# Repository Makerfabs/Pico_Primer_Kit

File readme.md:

# Pico(W) Primer Kit

```c++
/*
Version:		V1.8
Author:			Vincent
Create Date:	2021/4/16
Note:
	2022/12/30	V1.8 Edit Wiki Link
	2022/10/11 	V1.7 Add project11,12
	2022/10/8 	V1.6 Update project10
	2022/9/27 	V1.5 Add PicoW support, add new Mabee CO2
	2022/9/20 	V1.4 Fix dht11 bug.
	2021/7/27 	V1.3 Add WS2812
	2021/5/24 	V1.2 Change IR to Ultar distance sensor.
	2021/5/19 	V1.1 Add 7 display example with MaBee module.
	
*/
```

[toc]

# Makerfabs

[Makerfabs home page](https://www.makerfabs.com/)

[Makerfabs Wiki](https://wiki.makerfabs.com/)

# Pico(PicoW) Primer Kit
## Intruduce

### Product Link ：

[Pico Primer Kit for Raspberry PI](https://www.makerfabs.com/raspberry-pi-pico-primer-kit.html)

[Pico W Primer Kit for Raspberry PI](https://www.makerfabs.com/pico-w-primer-kit-for-raspberry-pi.html)

### Wiki Link : 

[Pico W_Primer_kit](https://wiki.makerfabs.com/Pico_W_Primer_Kit.html)

Pico Primer Kit is the development shield of Pi Pico. It has ST7735 color screen, 3 LED lights and 3 buttons. There are multiple SPI, I2C, UART, GPIO interfaces.
Kit contains a number of MBEE series modules. Such as potentiometer, DHT11, MPU6050, relay and other modules.

**Now that we have a new kit for Pico W, we have replaced the 8266 module with Mabee CO2.**

Most routines are compatible, the only differences are those related to WiFi.

## Feature

- RP2040 microcontroller chip designed by Raspberry Pi in the United Kingdom
- Dual-core Arm Cortex M0+ processor, the flexible clock running up to 133 MHz
- 264KB of SRAM, and 2MB of onboard Flash memory
- Castellated module allows soldering direct to carrier boards
- USB 1.1 with device and host support
- Low-power sleep and dormant modes
- Drag-and-drop programming using mass storage over USB
- 26 × multi-function GPIO pins
- 2 × SPI, 2 × I2C, 2 × UART, 3 × 12-bit ADC, 16 × controllable PWM channels
- Accurate clock and timer on-chip
- Temperature sensor
- Accelerated floating-point libraries on-chip
- 8 × Programmable I/O (PIO) state machines for custom peripheral support

### Front:

### Back:

# Example
## Equipment list

- Pico Primer Kit
- Pi Pico
- MBee modules

## How To Use?

Attention, all code depends on MicroPython v1.19.1 on 2022-08-19

**Subsequent code may not run due to MicroPython version updates. We provide two firmware.**

- Pico		:	rp2-pico-20220618-v1.19.1.uf2

- PicoW	:	rp2-pico-w-20220819-unstable-v1.19.1-298-gc616721b1.uf2

Because PicoW MicroPython has not been officially released, so the driver of the sensor, subject to the Pico.

**If you have any questions，such as how to install the development board, how to download the code.**

**Please refer to :[Get Started with MicroPython on Raspberry Pi Pico](https://hackspace.raspberrypi.org/books/micropython-pico)**

## V1.2 Project

### project-1-display_led_button.py

Control onboard leds via buttons.
And display status on TFT screen.
Don't need any module

### project-2-leveling.py

Simple graphic level, read inclination angle with MPU6050.
Insert MaBee MPU6050 to CN3

### project-3-adc_display.py

The voltage value of the read slide potentimeter is displayed on the screen
Insert MaBee Slide Potentimeter to CN5

### project-4-weather_8266.py

Connect to WiFi through ESP8266 module and get the weather.
Insert MaBee 8266 to CN1
API from "api.openweathermap.org" is not stable, please try more and pay attention to the serial port information.

### project-5-temperature .py

The temperature and humidity are obtained through DHT11 and displayed on the screen
Insert MaBee DHT11 to CN6

### ~~project-6-ir_distance.py~~

~~The distance is captured by a Sharpir sensor and displayed on the screen~~
~~Insert SharpIR to CN5~~

### project-6-HC-SR04_distance.py

The distance is captured by a HC-SR04 Ultra sensor and displayed on the screen
Insert SharpIR to CN6

### project-7-servo_control.py

Use button control servo and MaBee relay
Insert Servo to CN6
Insert MaBee Relay to CN5

### project-8-ws2812.py
Insert WS2812 to CN6

### project-9-weather.py

Instead of Project 4 without 8266.

**Only for Pico W**

### project-10-CO2.py

Mabee CO2 message display and run a webserver.

Insert Mabee CO2 to CN3, sda to GPIO8, scl to GPIO9

Need change WiFi config in code.

```python
ssid = 'Makerfabs'
password = '20160704'
```

### project-11-thingspeak.py

A simple example is sending data to ThingSpeak. 

Please replace the Wifi information and Thingspeak interface with the user's own.

**Only for Pico W**

### project-12-PIR_detection.py

PIR induction Demo, when the sensor detects the human body after alarm.

## Other test file

All files starting with Test are used by engineers and are not guaranteed to be completely correct. 

But it has some reference value.

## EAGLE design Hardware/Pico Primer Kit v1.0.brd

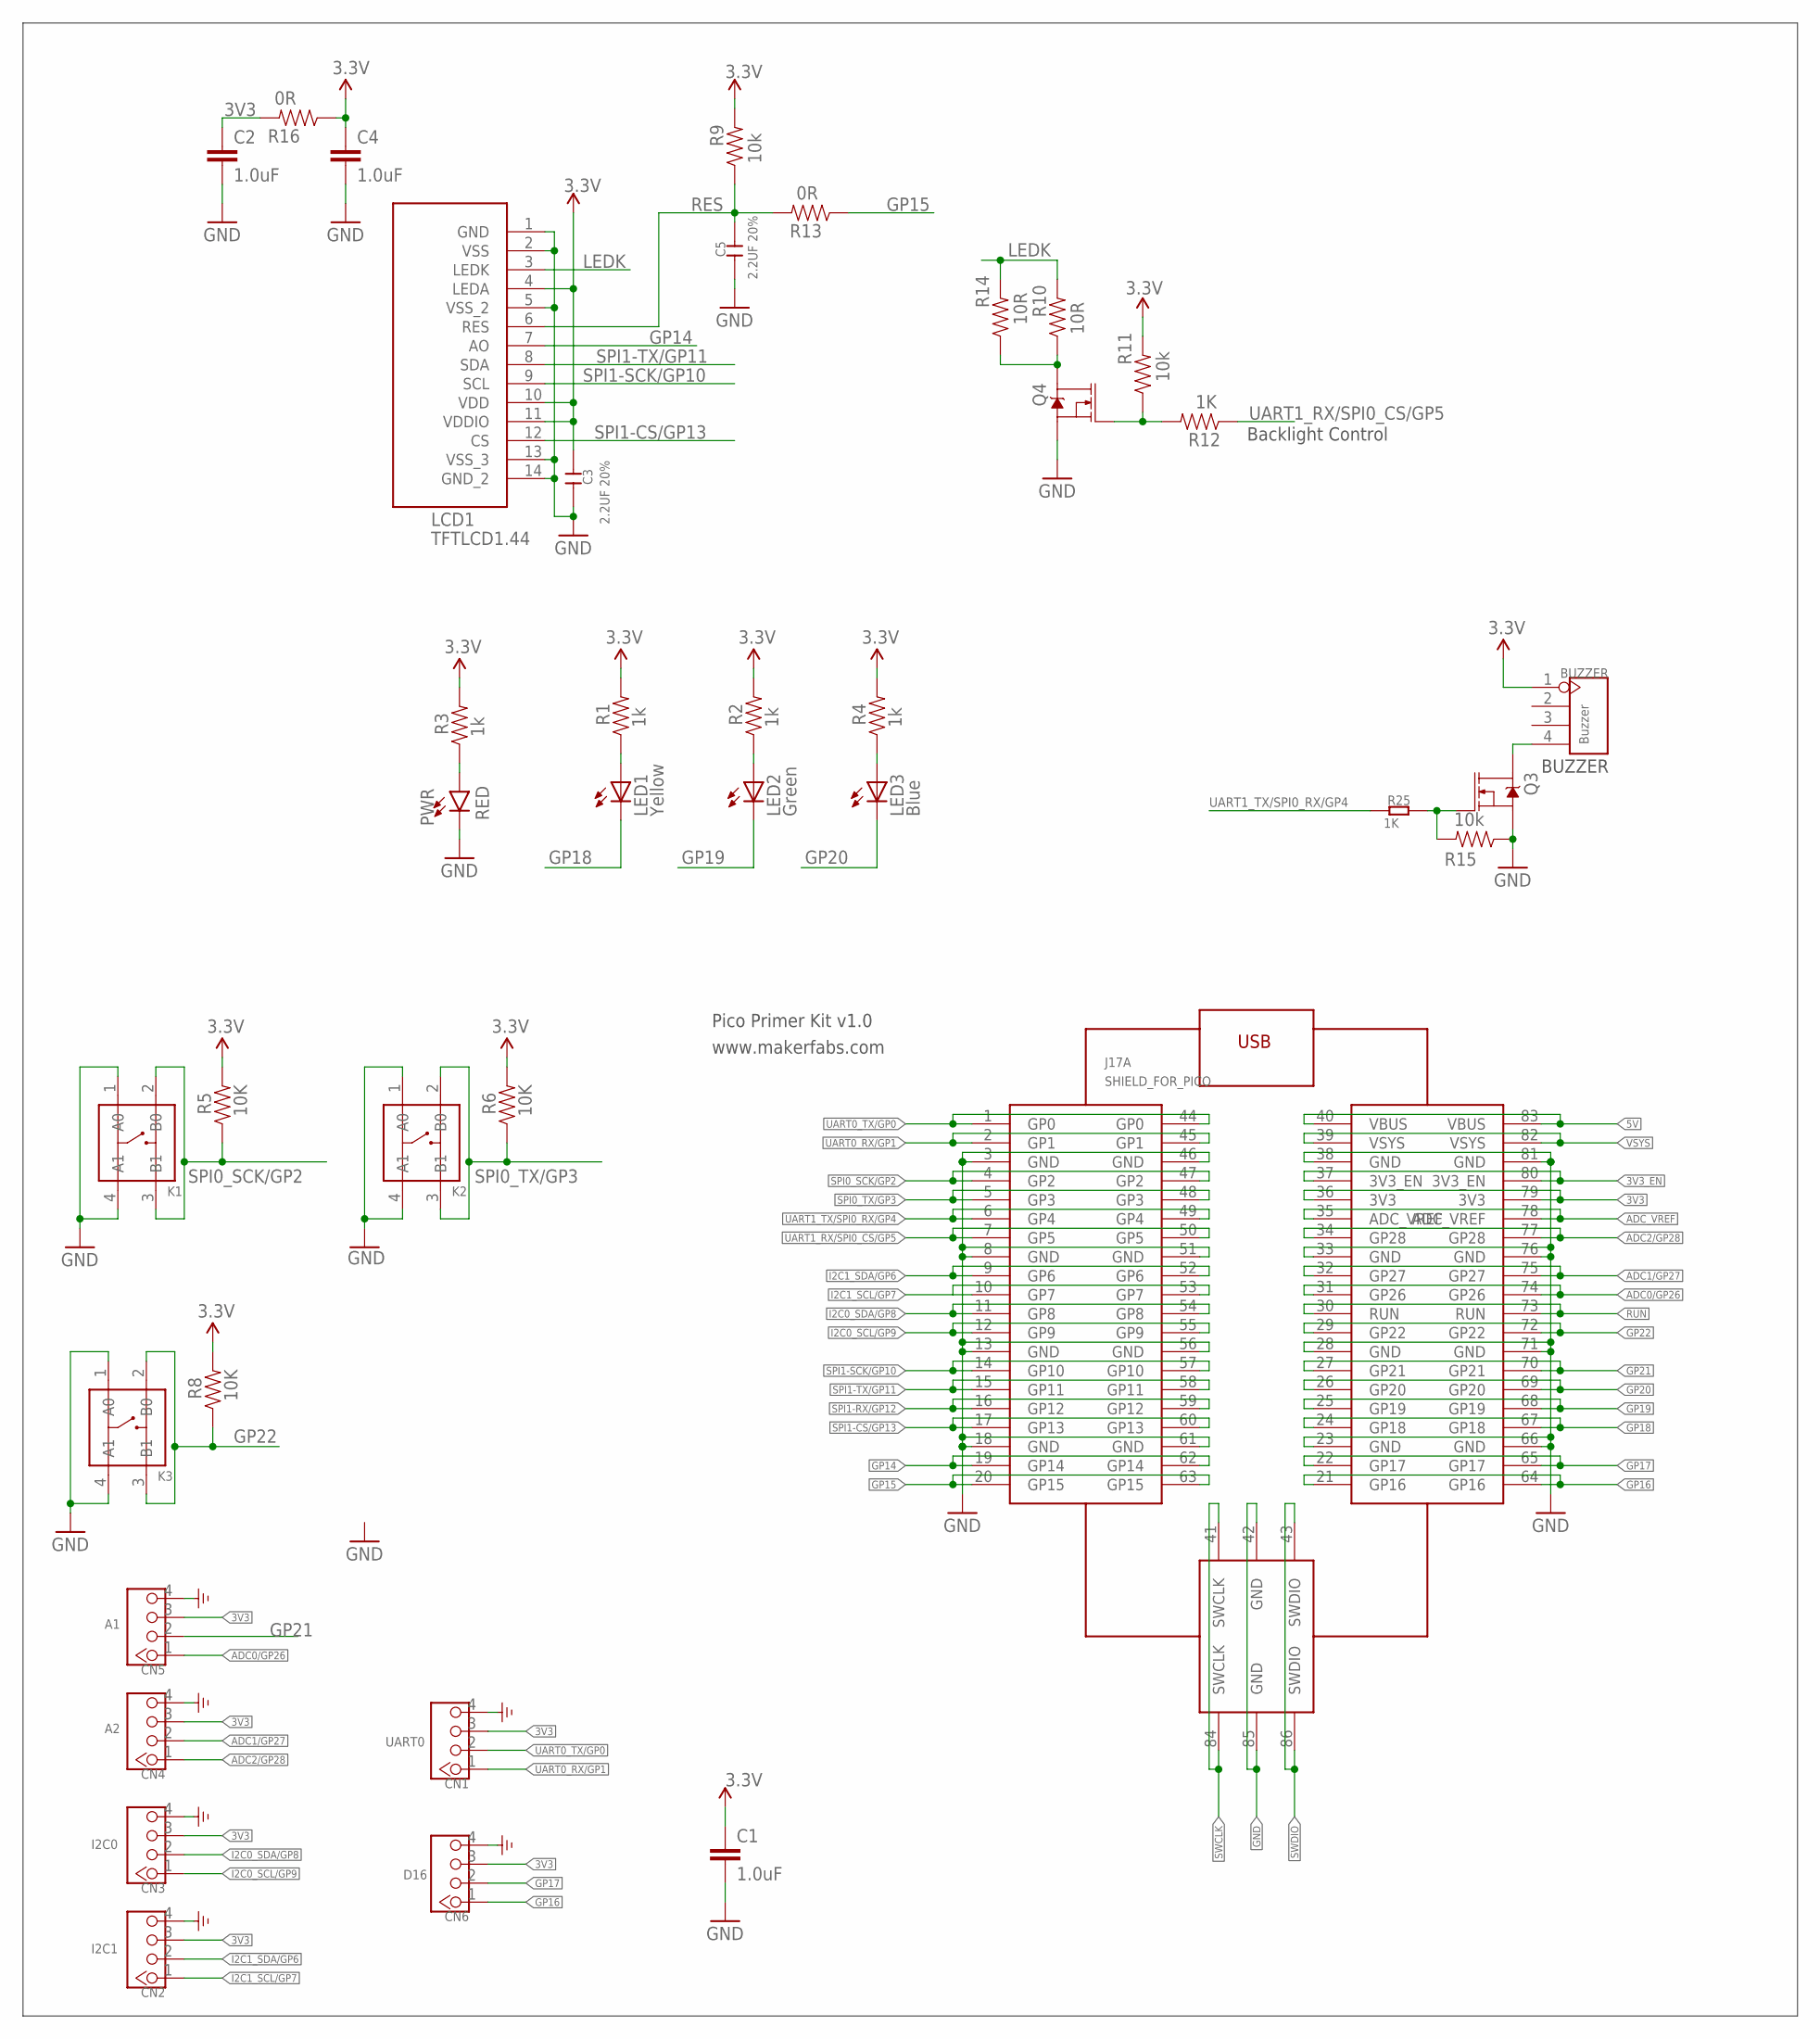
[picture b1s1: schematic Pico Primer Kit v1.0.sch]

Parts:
BUZZER: Buzzer; 4P-65/35ROUND
C1, C2, C4: 1.0uF; 0603
C3, C5: 2.2UF 20%; 0603
CN1: UART0; 4P-2.0
CN2: I2C1; 4P-2.0
CN3: I2C0; 4P-2.0
CN4: A2; 4P-2.0
CN5: A1; 4P-2.0
CN6: D16; 4P-2.0
J17A: SHIELD_FOR_PICO
K1, K2, K3: BUTTON-4P-3100010P1; 4P-SMD-6.0X6.0X5.0H
LCD1: TFTLCD1.44
LED1: Yellow; LED3MM
LED2: Green; LED3MM
LED3: Blue; LED3MM
PWR: RED; LED-0603
Q3, Q4: 220mA/50V/3.5Ω; SOT23-3
R1, R2, R3, R4: 1k; 0603
R5, R6, R8: 10K; 0603
R9, R11, R15: 10k; 0603
R10, R14: 10R; 0603
R12: 1K; 0603
R13, R16: 0R; 0603
R25: 1K; R0603

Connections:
3.3V: BUZZER.1, C1.1, C3.2, C4.1, LCD1.4 (LEDA), LCD1.10 (VDD), LCD1.11 (VDDIO), R1.2, R2.2, R3.2, R4.2, R5.2, R6.2, R8.2, R9.2, R11.2, R16.1
3V3: C2.1, CN1.3, CN2.3, CN3.3, CN4.3, CN5.3, CN6.3, J17A.36 (3V3), J17A.79 (3V3), R16.2
3V3_EN: J17A.37 (3V3_EN), J17A.80 (3V3_EN)
5V: J17A.40 (VBUS), J17A.83 (VBUS)
ADC0/GP26: CN5.1, J17A.31 (GP26), J17A.74 (GP26)
ADC1/GP27: CN4.2, J17A.32 (GP27), J17A.75 (GP27)
ADC2/GP28: CN4.1, J17A.34 (GP28), J17A.77 (GP28)
ADC_VREF: J17A.35 (ADC_VREF), J17A.78 (ADC_VREF)
GND: C1.2, C2.2, C3.1, C4.2, C5.1, CN1.4, CN2.4, CN3.4, CN4.4, CN5.4, CN6.4, J17A.3 (GND), J17A.8 (GND), J17A.13 (GND), J17A.18 (GND), J17A.23 (GND), J17A.28 (GND), J17A.33 (GND), J17A.38 (GND), J17A.42 (GND), J17A.46 (GND), J17A.51 (GND), J17A.56 (GND), J17A.61 (GND), J17A.66 (GND), J17A.71 (GND), J17A.76 (GND), J17A.81 (GND), J17A.85 (GND), K1.1 (A0), K1.4 (A1), K2.1 (A0), K2.4 (A1), K3.1 (A0), K3.4 (A1), LCD1.1 (GND), LCD1.2 (VSS), LCD1.5 (VSS_2), LCD1.13 (VSS_3), LCD1.14 (GND_2), PWR.C, Q3.2 (S), Q4.2 (S), R15.1
GP14: J17A.19 (GP14), J17A.62 (GP14), LCD1.7 (AO)
GP15: J17A.20 (GP15), J17A.63 (GP15), R13.1
GP16: CN6.1, J17A.21 (GP16), J17A.64 (GP16)
GP17: CN6.2, J17A.22 (GP17), J17A.65 (GP17)
GP18: J17A.24 (GP18), J17A.67 (GP18), LED1.K (C)
GP19: J17A.25 (GP19), J17A.68 (GP19), LED2.K (C)
GP20: J17A.26 (GP20), J17A.69 (GP20), LED3.K (C)
GP21: CN5.2, J17A.27 (GP21), J17A.70 (GP21)
GP22: J17A.29 (GP22), J17A.72 (GP22), K3.2 (B0), K3.3 (B1), R8.1
I2C0_SCL/GP9: CN3.1, J17A.12 (GP9), J17A.55 (GP9)
I2C0_SDA/GP8: CN3.2, J17A.11 (GP8), J17A.54 (GP8)
I2C1_SCL/GP7: CN2.1, J17A.10 (GP7), J17A.53 (GP7)
I2C1_SDA/GP6: CN2.2, J17A.9 (GP6), J17A.52 (GP6)
LEDK: LCD1.3 (LEDK), R10.2, R14.2
unnamed: LED1.A, R1.1
unnamed: PWR.A, R3.1
unnamed: Q4.3 (D), R10.1, R14.1
unnamed: Q4.1 (G), R11.1, R12.2
unnamed: LED2.A, R2.1
unnamed: LED3.A, R4.1
unnamed: BUZZER.4, Q3.3 (D)
unnamed: Q3.1 (G), R15.2, R25.2
RES: C5.2, LCD1.6 (RES), R9.1, R13.2
RUN: J17A.30 (RUN), J17A.73 (RUN)
SPI0_SCK/GP2: J17A.4 (GP2), J17A.47 (GP2), K1.2 (B0), K1.3 (B1), R5.1
SPI0_TX/GP3: J17A.5 (GP3), J17A.48 (GP3), K2.2 (B0), K2.3 (B1), R6.1
SPI1-CS/GP13: J17A.17 (GP13), J17A.60 (GP13), LCD1.12 (CS)
SPI1-RX/GP12: J17A.16 (GP12), J17A.59 (GP12)
SPI1-SCK/GP10: J17A.14 (GP10), J17A.57 (GP10), LCD1.9 (SCL)
SPI1-TX/GP11: J17A.15 (GP11), J17A.58 (GP11), LCD1.8 (SDA)
SWCLK: J17A.41 (SWCLK), J17A.84 (SWCLK)
SWDIO: J17A.43 (SWDIO), J17A.86 (SWDIO)
UART0_RX/GP1: CN1.1, J17A.2 (GP1), J17A.45 (GP1)
UART0_TX/GP0: CN1.2, J17A.1 (GP0), J17A.44 (GP0)
UART1_RX/SPI0_CS/GP5: J17A.7 (GP5), J17A.50 (GP5), R12.1
UART1_TX/SPI0_RX/GP4: J17A.6 (GP4), J17A.49 (GP4), R25.1
VSYS: J17A.39 (VSYS), J17A.82 (VSYS)

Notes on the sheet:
Pico Primer Kit v1.0
www.makerfabs.com
BUZZER
Backlight Control

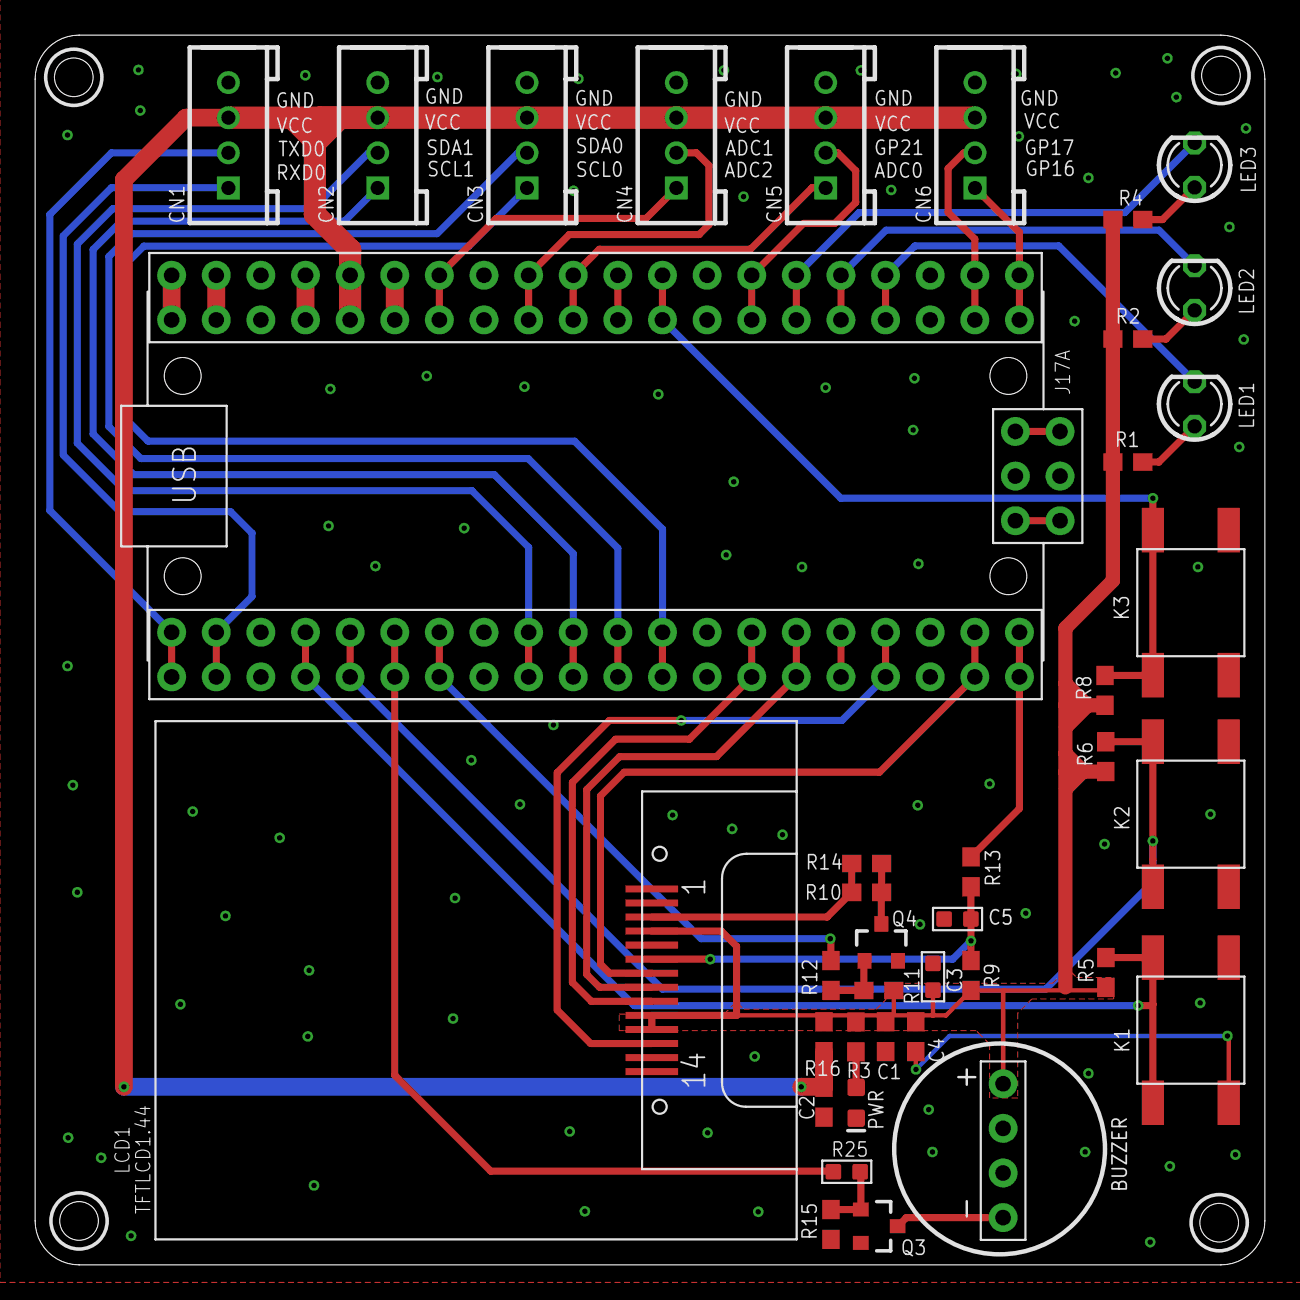
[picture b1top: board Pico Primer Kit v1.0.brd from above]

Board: 2 copper layers, 70.0 x 70.0 mm, 40 parts (1 on the bottom side), 46 nets.

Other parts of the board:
U$1: MAKERFABS_0.3

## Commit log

2021-04-16 V1.0
2021-05-13 Add some display example
2021-05-18 Add new project
2021-05-19 edit readme
2021-05-20 Fix 8266 bug.
2021-05-24 fix bug
2021-06-07 add Arduino display demo
2021-06-07 create hardware
2021-07-27 Add WS2812
2021-07-27 Add pic
2022-01-06 Fix Change the string matching mode to regular expression matching.
2022-03-03 Update readme.md
    update wiki link
2022-08-25 Add pico W support
2022-09-20 V1.4
2022-09-27 Add mabee co2 support
2022-09-27 V1.5
2022-10-08 Update project10
2022-10-10 Organize file locations
2022-10-11 Add pir demo

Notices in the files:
parts and their libraries:
SparkFun-Capacitors: Licensing: Creative Commons ShareAlike 4.0 International - https://creativecommons.org/licenses/by-sa/4.0
